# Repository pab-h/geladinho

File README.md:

# ❄️ Projeto Geladinho

**Sistema Embarcado de Resfriamento de Líquido Controlado com ESP32**

O **Geladinho** é um projeto de firmware para controle preciso de temperatura de líquidos. O sistema utiliza um módulo Peltier para resfriamento, tudo gerenciado por um ESP32 rodando **FreeRTOS** com uma arquitetura em camadas (HAL, Tasks, Application).

---

## 🚀 Funcionalidades

- **Monitoramento de Temperatura:** Leitura contínua via termistor NTC (ou simulação via LDR).
- **Controle de Resfriamento:** Atuação sobre pastilha Peltier (futuro: controle PID/ON-OFF).
- **Agitação:** Controle de motor para movimentação do líquido.
- **Interface:** Feedback visual via LCD e sonoro via Buzzer.
- **Multitarefa Real-Time:** Arquitetura baseada em FreeRTOS para não-bloqueio.

---

## 🛠️ Hardware

- **MCU:** ESP32 (DevKit V1 / Upesy Wroom)
- **Sensor:** Termistor NTC 10k (Beta 3380)
- **Atuador Térmico:** Pastilha Peltier (com Driver/Relé)
- **Agitador:** Motor DC
- **Display:** Oled

---

## 🏗️ Arquitetura de Software

O projeto segue o princípio de **separação de responsabilidades**:

```text
├── src/
│   ├── app/           # Lógica de Negócio e Estado Global (State Machine)
│   ├── hal/           # Hardware Abstraction Layer (Drivers diretos do ESP32)
│   ├── tasks/         # Tarefas do FreeRTOS (Loops infinitos)
│   ├── freertos/      # Configurações do SO
│   └── main.cpp       # Entry point (Setup do Hardware e Tasks)
└── lib/               # Bibliotecas auxiliares
```

## 👥 Autores

Este projeto foi desenvolvido com a colaboração de:

<table>
  <tr>
    <td align="center">
      <a href="https://github.com/Miguel-Edson">
        
        <br />
        <sub><b>Miguel Edson</b></sub>
      </a>
    </td>
    <td align="center">
      <a href="https://github.com/pab-h">
        
        <br />
        <sub><b>pab-h</b></sub>
      </a>
    </td>
  </tr>
</table>

---

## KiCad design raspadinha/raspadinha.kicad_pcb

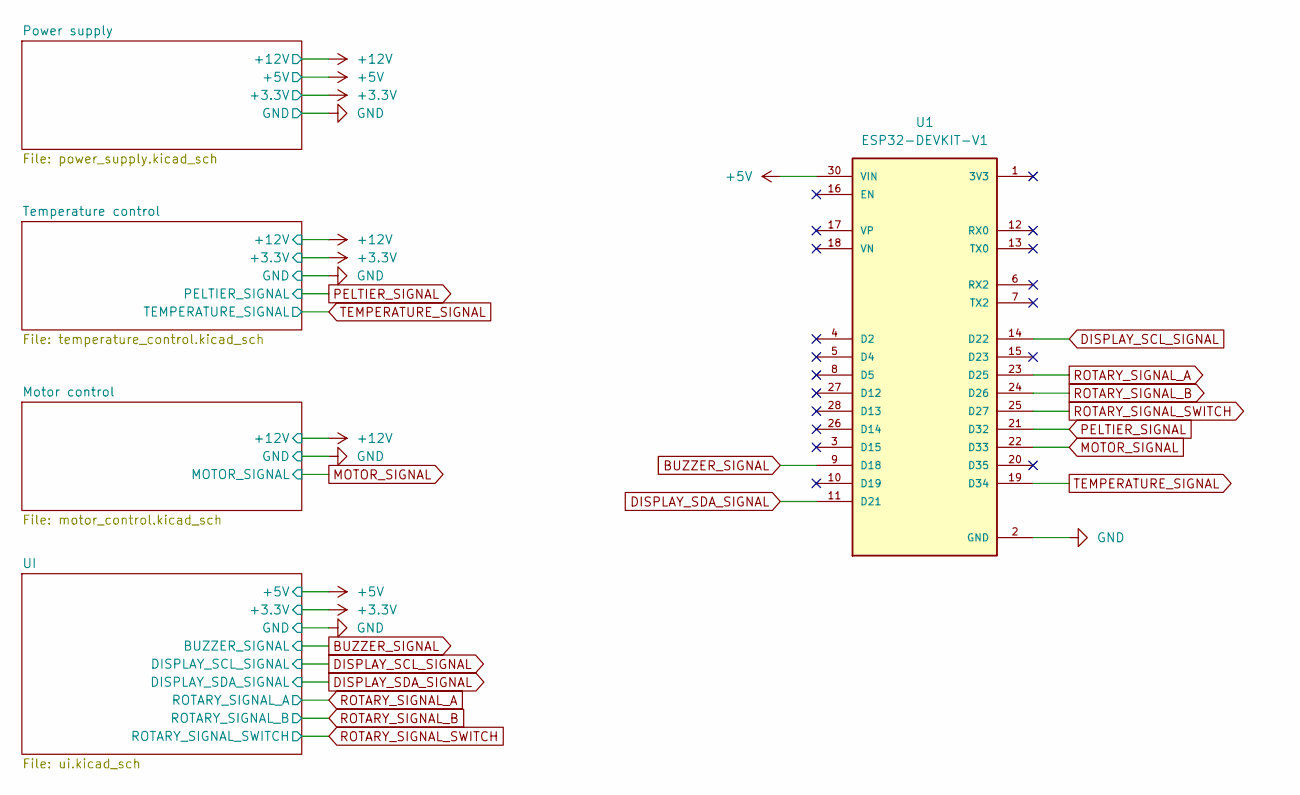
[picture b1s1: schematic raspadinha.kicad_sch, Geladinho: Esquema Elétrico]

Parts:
U1: ESP32-DEVKIT-V1; MODULE_ESP32_DEVKIT_V1; PARTREV N/A

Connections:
+5V: U1.30 (VIN); also elsewhere on the board
BUZZER_SIGNAL: U1.9 (D18); also elsewhere on the board
DISPLAY_SCL_SIGNAL: U1.14 (D22); also elsewhere on the board
DISPLAY_SDA_SIGNAL: U1.11 (D21); also elsewhere on the board
GND: U1.2 (GND), U1.29 (GND); also elsewhere on the board
MOTOR_SIGNAL: U1.22 (D33); also elsewhere on the board
PELTIER_SIGNAL: U1.21 (D32); also elsewhere on the board
ROTARY_SIGNAL_A: U1.23 (D25); also elsewhere on the board
ROTARY_SIGNAL_B: U1.24 (D26); also elsewhere on the board
ROTARY_SIGNAL_SWITCH: U1.25 (D27); also elsewhere on the board
TEMPERATURE_SIGNAL: U1.19 (D34); also elsewhere on the board

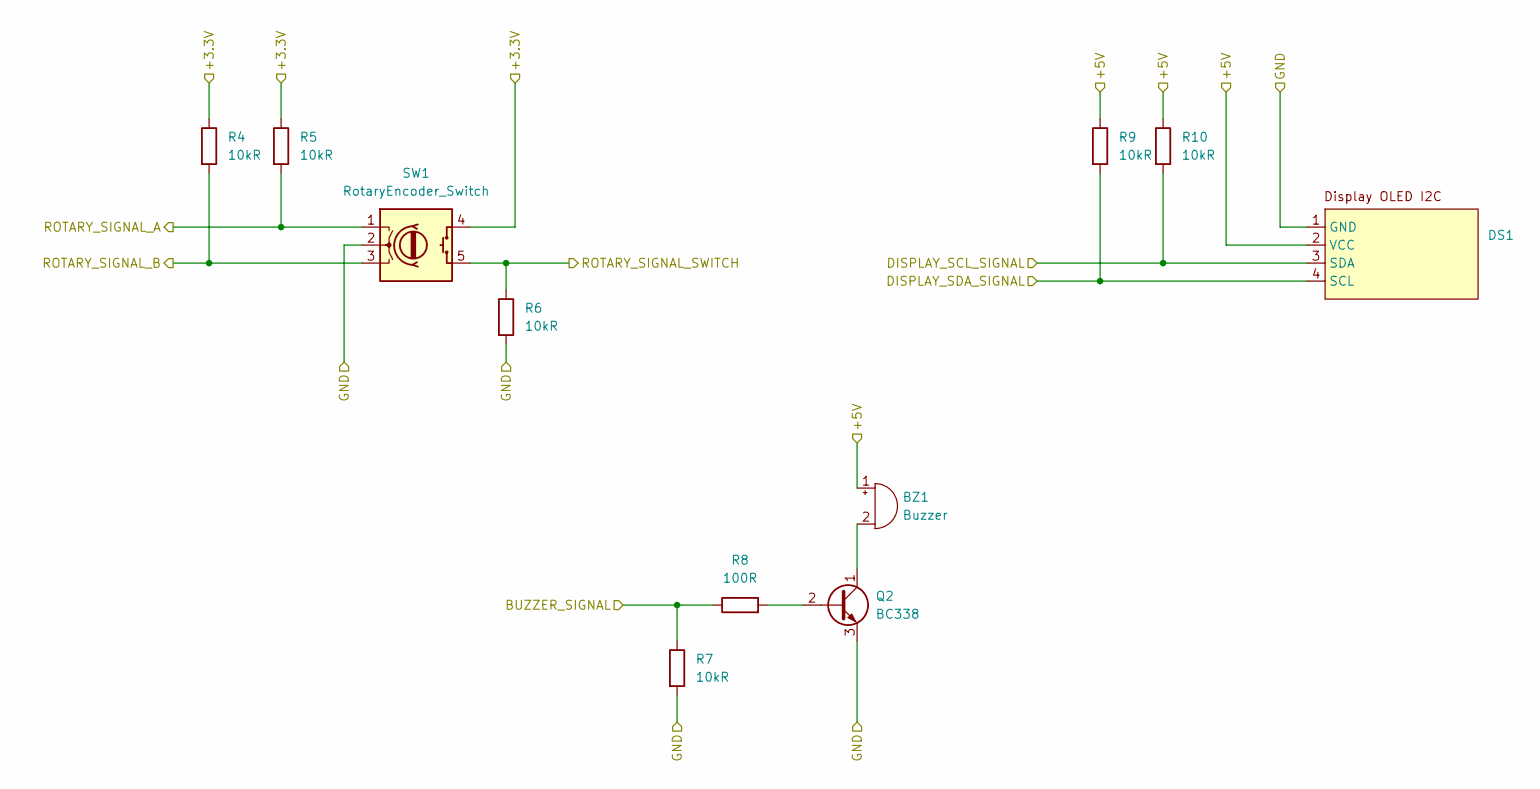
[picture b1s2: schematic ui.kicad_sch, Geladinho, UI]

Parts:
BZ1: Buzzer; MagneticBuzzer_ProSignal_ABT-410-RC
DS1: PinHeader_1x04_P2.54mm_Vertical
Q2: BC338; TO-92_Inline
R4, R5, R6, R7, R9, R10: 10kR; R_Axial_DIN0411_L9.9mm_D3.6mm_P12.70mm_Horizontal
R8: 100R; R_Axial_DIN0411_L9.9mm_D3.6mm_P12.70mm_Horizontal
SW1: RotaryEncoder_Switch; PinHeader_1x05_P2.54mm_Vertical

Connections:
+3.3V: R4.1, R5.1, SW1.4 (S1); also elsewhere on the board
+5V: BZ1.1 (+), DS1.2 (VCC), R9.1, R10.1; also elsewhere on the board
BUZZER_SIGNAL: R7.1, R8.1; also elsewhere on the board
DISPLAY_SCL_SIGNAL: DS1.3 (SDA), R10.2; also elsewhere on the board
DISPLAY_SDA_SIGNAL: DS1.4 (SCL), R9.2; also elsewhere on the board
GND: DS1.1 (GND), Q2.3 (E), R6.2, R7.2, SW1.2 (C); also elsewhere on the board
unnamed: BZ1.2 (-), Q2.1 (C)
unnamed: Q2.2 (B), R8.2
ROTARY_SIGNAL_A: R5.2, SW1.1 (A); also elsewhere on the board
ROTARY_SIGNAL_B: R4.2, SW1.3 (B); also elsewhere on the board
ROTARY_SIGNAL_SWITCH: R6.1, SW1.5 (S2); also elsewhere on the board

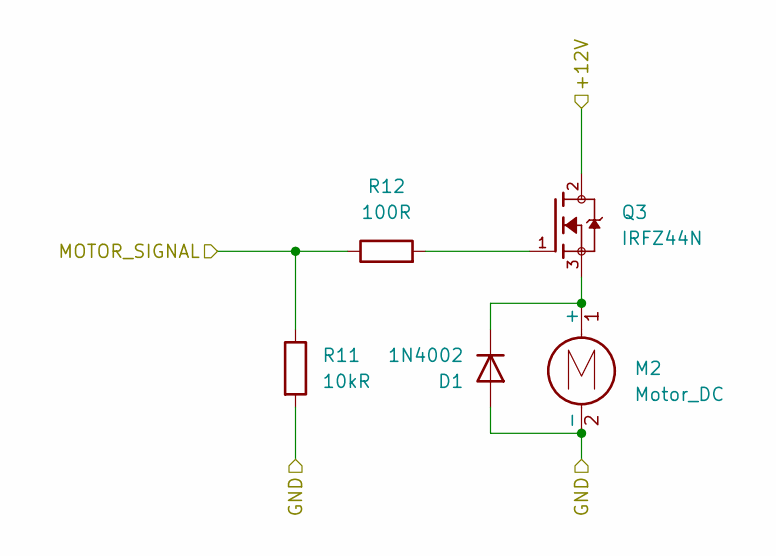
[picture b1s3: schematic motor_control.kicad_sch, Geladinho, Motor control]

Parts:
D1: 1N4002; D_DO-41_SOD81_P10.16mm_Horizontal
M2: Motor_DC; TerminalBlock_Phoenix_PT-1,5-2-3.5-H_1x02_P3.50mm_Horizontal
Q3: IRFZ44N; TO254P1016X419X2286-3; PARTREV 09/21/10
R11: 10kR; R_Axial_DIN0411_L9.9mm_D3.6mm_P12.70mm_Horizontal
R12: 100R; R_Axial_DIN0411_L9.9mm_D3.6mm_P12.70mm_Horizontal

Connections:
+12V: Q3.2; also elsewhere on the board
GND: D1.2 (A), M2.2 (-), R11.2; also elsewhere on the board
MOTOR_SIGNAL: R11.1, R12.1; also elsewhere on the board
unnamed: D1.1 (K), M2.1 (+), Q3.3
unnamed: Q3.1, R12.2

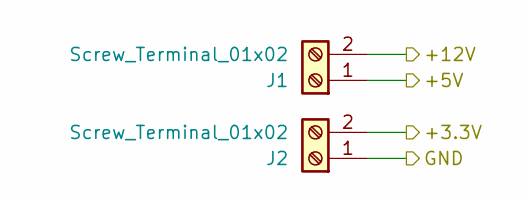
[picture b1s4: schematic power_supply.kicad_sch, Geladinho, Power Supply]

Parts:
J1, J2: Screw_Terminal_01x02; TerminalBlock_Phoenix_PT-1,5-2-3.5-H_1x02_P3.50mm_Horizontal

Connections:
+3.3V: J2.2; also elsewhere on the board
+5V: J1.1; also elsewhere on the board
+12V: J1.2; also elsewhere on the board
GND: J2.1; also elsewhere on the board

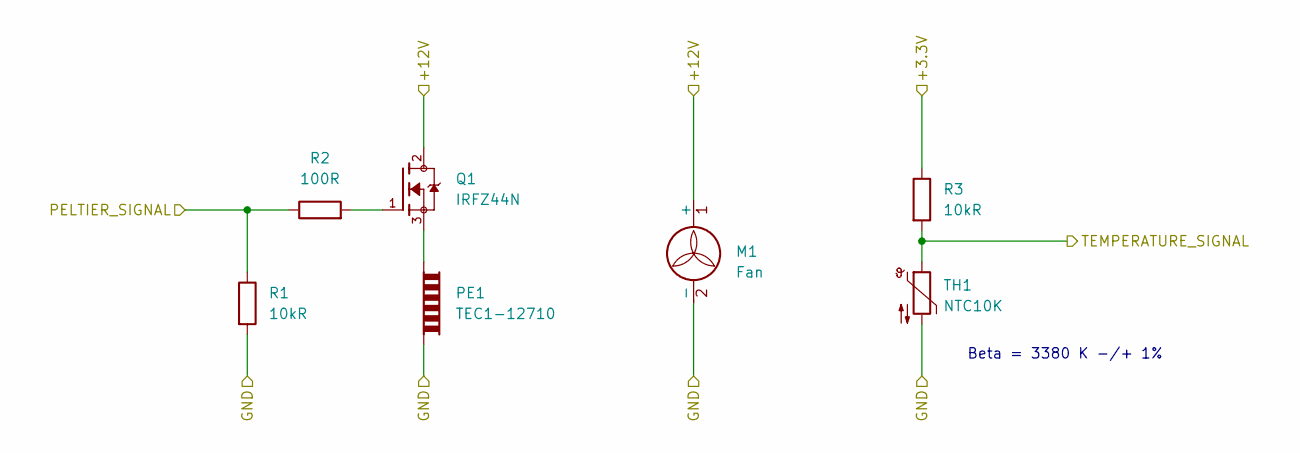
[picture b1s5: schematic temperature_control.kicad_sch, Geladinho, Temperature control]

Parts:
M1: Fan; Molex_KK-254_AE-6410-02A_1x02_P2.54mm_Vertical
PE1: TEC1-12710; TerminalBlock_Phoenix_PT-1,5-2-3.5-H_1x02_P3.50mm_Horizontal
Q1: IRFZ44N; TO254P1016X419X2286-3; PARTREV 09/21/10
R1, R3: 10kR; R_Axial_DIN0411_L9.9mm_D3.6mm_P12.70mm_Horizontal
R2: 100R; R_Axial_DIN0411_L9.9mm_D3.6mm_P12.70mm_Horizontal
TH1: NTC10K; Molex_KK-254_AE-6410-02A_1x02_P2.54mm_Vertical

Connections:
+3.3V: R3.1; also elsewhere on the board
+12V: M1.1 (+), Q1.2; also elsewhere on the board
GND: M1.2 (-), PE1.2, R1.2, TH1.2; also elsewhere on the board
unnamed: PE1.1, Q1.3
unnamed: Q1.1, R2.2
PELTIER_SIGNAL: R1.1, R2.1; also elsewhere on the board
TEMPERATURE_SIGNAL: R3.2, TH1.1; also elsewhere on the board

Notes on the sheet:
Beta = 3380 K -/+ 1%

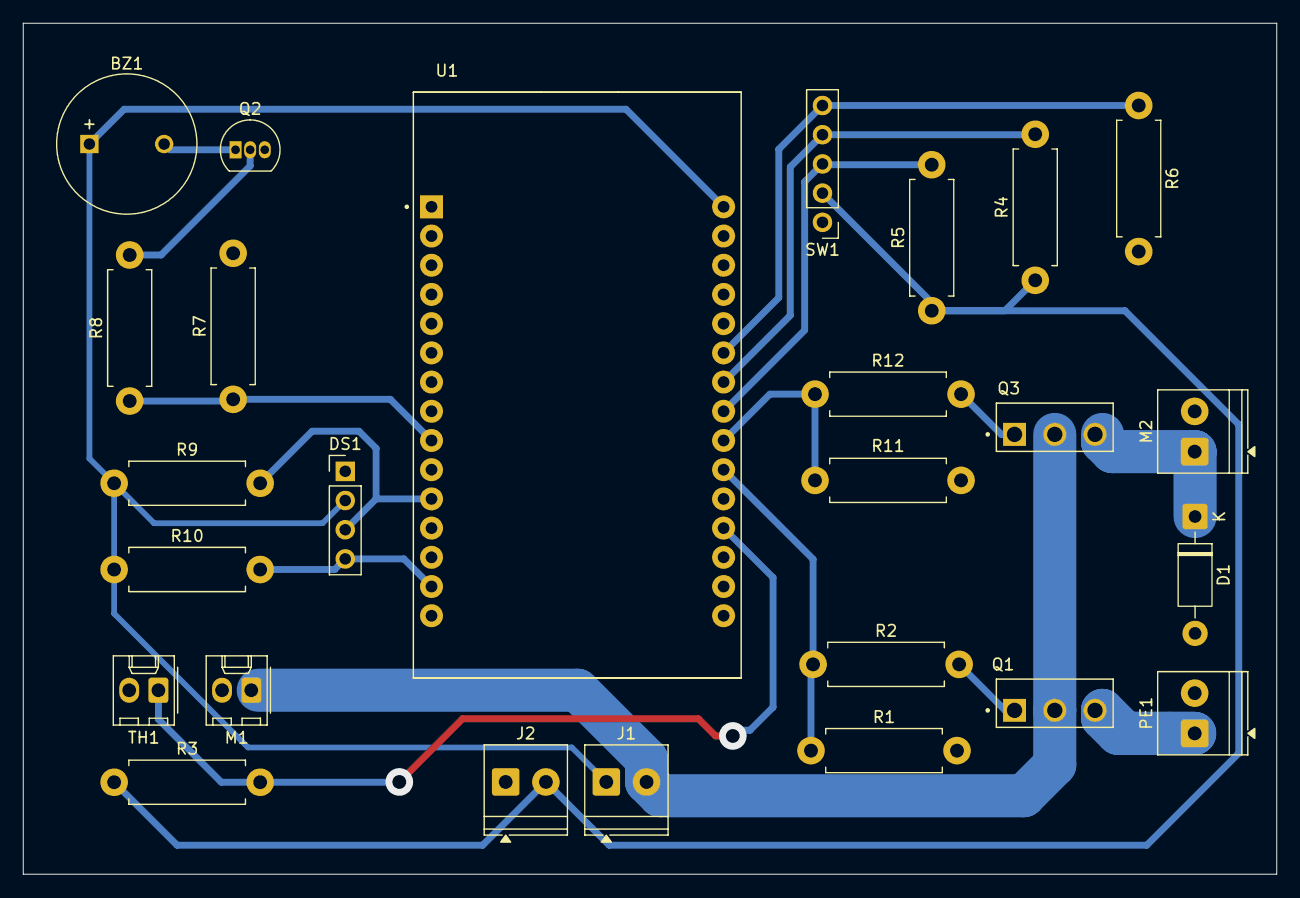
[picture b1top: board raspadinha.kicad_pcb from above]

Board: 2 copper layers, 109.0 x 74.0 mm, 26 parts (0 on the bottom side), 19 nets.

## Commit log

2025-10-24 feat: Diagramação elétrica da fonte de alimentação
2025-10-24 Fix: Esqueci de por o gitignore
2025-10-27 feat: Atualização dos datasheets
2025-10-27 feat: Novos arquivos temporários que são criados quando o KiCad está aberto
2025-10-27 feat: Esquema elétrico do controle de temperatura
2025-10-27 docs: Correntes máximas
2025-10-31 feat: Circuito de controle do Motor
2025-11-20 feat: Eletrônica da interface
2025-11-20 feat: Modularização do esquema elétrico
2025-11-21 feat: modelo da esp32
2025-11-21 feat: Conexões da ESP32
2025-11-21 feat: diretório de arquivos gerados pelo kicad
2025-11-30 feat: usando o mosfet IRFZ44N feat: switch de on/off na fonte de alimentação
2025-11-30 feat: setup do platformio
2025-12-03 :bricks: setup project architecture and documentation
2025-12-06 :broom: cleanup Deleted drivers folder and renaming tasks folder
2025-12-06 Fix typo in README regarding file extensions
2025-12-06 :sparkles: feat: NTC sensor included
2025-12-15 :boom: fix: Fixing the freeRTOS missing problem!
2025-12-15 :broom: cleanup: Cleaning the code and fixing the pattern
2025-12-15 Revise README for Projeto Geladinho
    Updated README with project details, features, hardware, and authors.
2025-12-19 feat: Mudança no display utilizado
2025-12-21 :sparkles: feat: Added Peltier functions (hal and tasks) also, added the control tasks.
2025-12-21 :bookmark: saving to keep it saved while i fix another branch
2025-12-21 feat: Os Footprint foram todos atribuidos fix: A placa da Esp32 foi trocada pela que temos disponível
2025-12-21 :bug: fix: Fixing the details the dev asked
2025-12-22 feat: Posicionamento dos componentes na placa
2025-12-23 :sparkles: feat: Added status bar and opening screen
2025-12-23 feat: Refatoração da alimentação da placa feat: Renomeação do número dos componentes
2025-12-23 feat: NetClasses
2025-12-24 feat: Elementos roteados
2025-12-28 Remove RyamLael from contributors list
    Removed contributor section from README.
2025-12-28 :sparkles: feat: Added current status of temperature + Setting up the encouder branch
2025-12-28 :sparkles: feat: Added encoder feature, still on test version tho!
